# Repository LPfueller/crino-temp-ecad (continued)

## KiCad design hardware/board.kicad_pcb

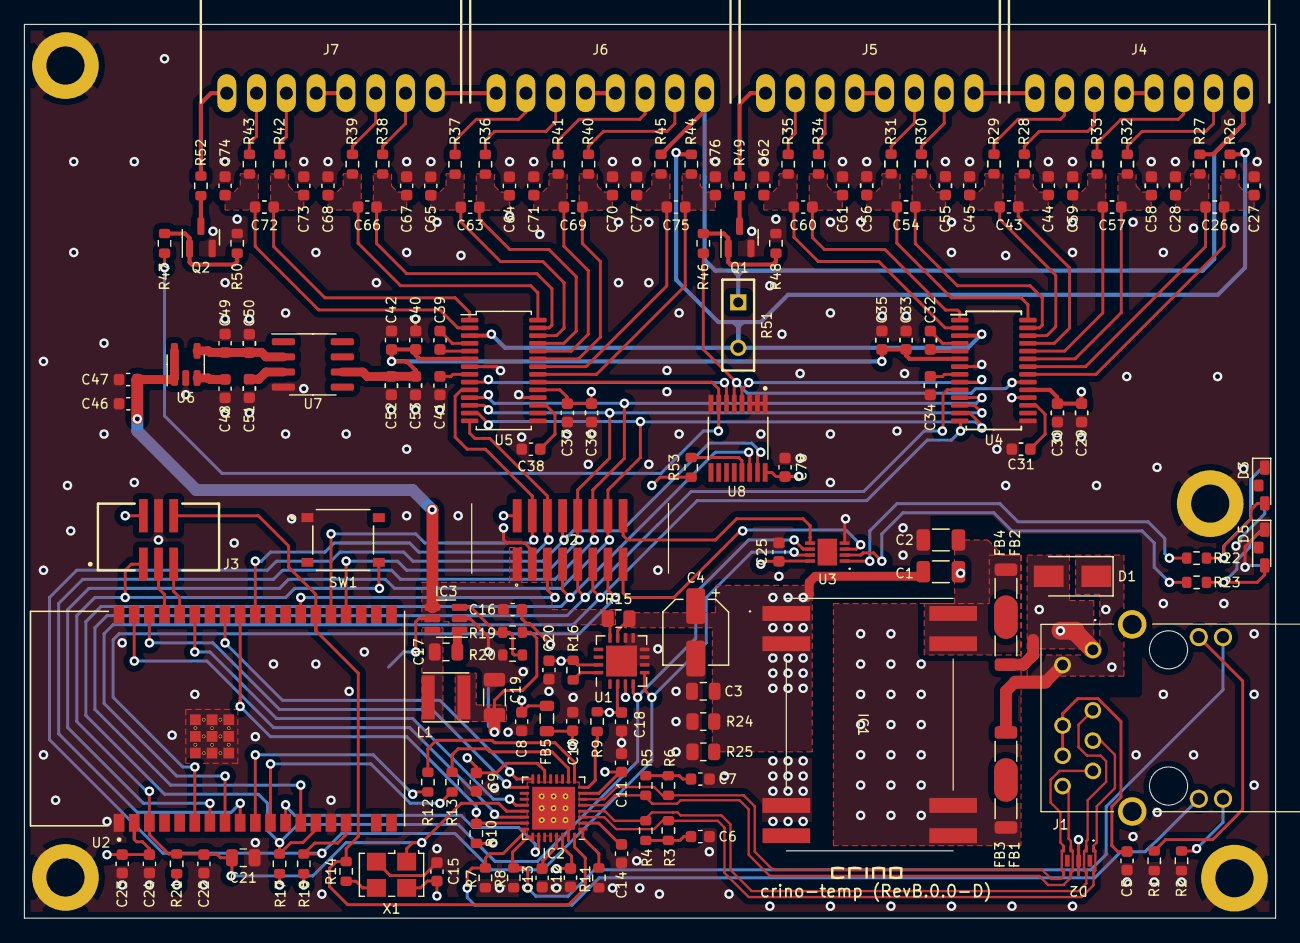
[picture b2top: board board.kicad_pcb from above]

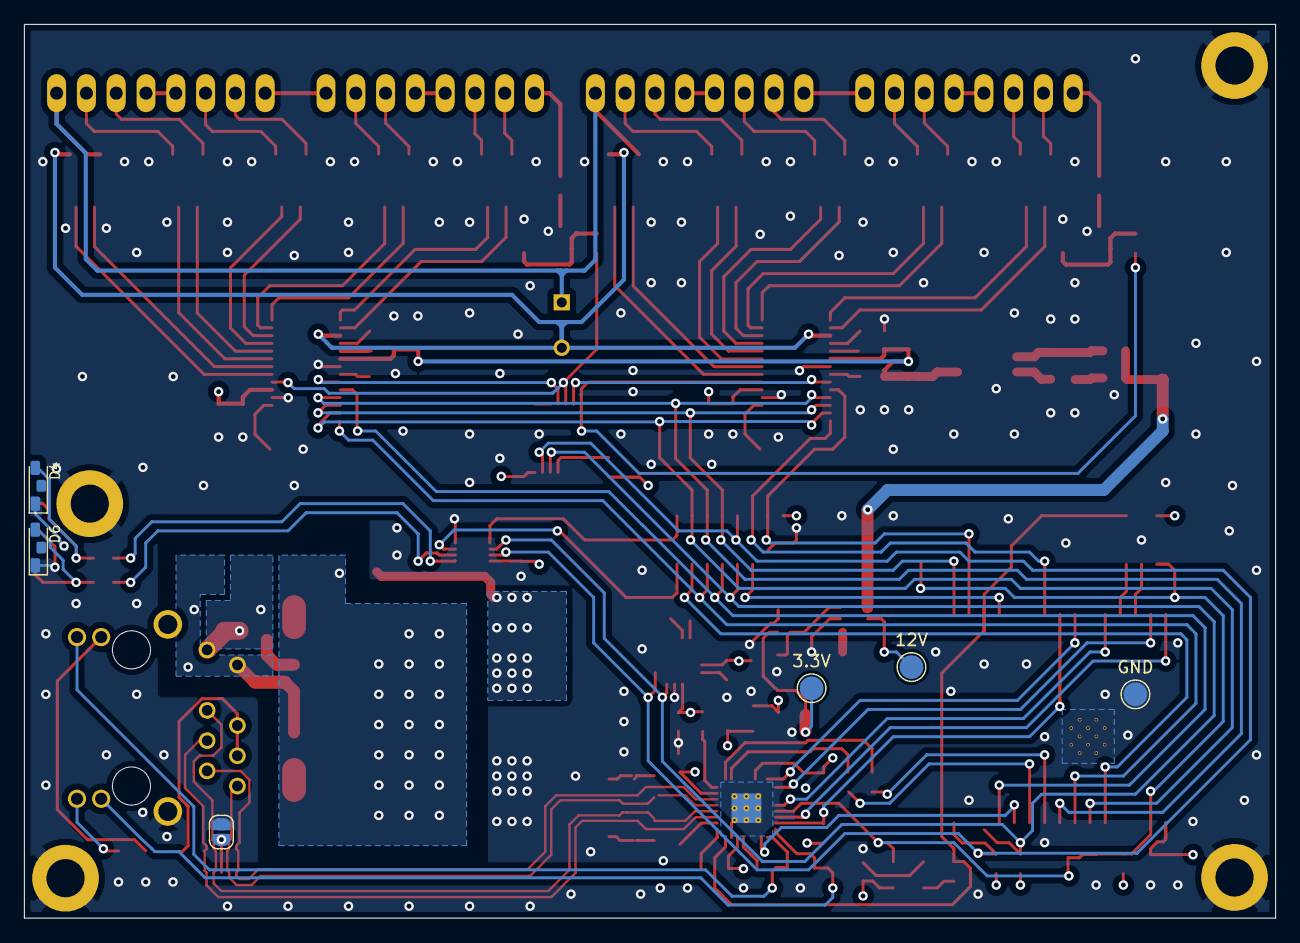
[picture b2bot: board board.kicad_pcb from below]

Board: 4 copper layers, 105.0 x 75.0 mm, 174 parts (6 on the bottom side), 130 nets.

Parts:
C1, C2: 4.7n; C_1206_3216Metric
C3: 10u; C_0805_2012Metric
C4: 100u; CP_Elec_5x5.4
C5: 22p; C_0603_1608Metric
C6, C7, C9, C11, C12, C13, C14, C15, C18, C20, C24, C25, C30, C33, C37, C40, C47, C48, C50, C53, C78: 100n; C_0603_1608Metric
C8, C10: 47u; C_0603_1608Metric
C16: 4.7u; C_0603_1608Metric
C17, C21: 100n; C_0805_2012Metric
C19: 22u; C_1206_3216Metric
C22, C29, C31, C34, C35, C36, C38, C41, C42, C51: 1u; C_0603_1608Metric
C23: 22u; C_0603_1608Metric
C26, C43, C54, C57, C60, C63, C66, C69, C72, C75: 22n; C_0603_1608Metric
C27, C28, C44, C45, C55, C56, C58, C59, C61, C62, C64, C65, C67, C68, C70, C71, C73, C74, C76, C77: 1n; C_0603_1608Metric
C32, C39: 4.7n; C_0603_1608Metric
C46, C49, C52: 2.2u; C_0603_1608Metric
D1: D_Schottky; D_SMA
D2: RCLAMP3374N.TCT; RCLAMP3374NTCT
D3, D4: LED_GREEN; LED_3210Metric_Right_Angle
D5, D6: LED_BLUE; LED_3210Metric_Right_Angle
FB1, FB2, FB3, FB4: FerriteBead; L_1206_3216Metric
FB5: FerriteBead; L_0805_2012Metric
H1, H2, H3, H4: MountingHole_Pad; MountingHole_3.2mm_M3_DIN965_Pad
H5: CrinoLogo; crino_logo
IC1: AG9912M
IC2: RTL8201F-VB-CG; QFN-32-1EP_5x5mm_P0.5mm_EP3.6x3.6mm_ThermalVias
IC3: SY8120B1ABC; SOT-23-6
J1: JXD1-0009NL; JXD10009NL
J2: SHF-108-01-L-D-SM; SHF-108-01-X-D-SM
J3: SHF-103-01-L-D-SM; SAMTEC_SHF-103-01-L-D-SM
J4, J5, J6, J7: WAGO-733-368; Wago_733-368
JP1: SolderJumper_2_Open; SolderJumper-2_P1.3mm_Open_RoundedPad1.0x1.5mm
L1: 4.7u; L_4.2x4.2_H2
Q1, Q2: 2N7002; SOT-23
R1, R2: 270; R_0603_1608Metric
R3, R4, R5, R6: 49.9; R_0603_1608Metric
R7, R8, R9, R10: 4.7k; R_0603_1608Metric
R11: 2.49k; R_0603_1608Metric
R12, R13, R14: 0; R_0603_1608Metric
R15: 0.68; R_0805_2012Metric
R16: 2.2k; R_0603_1608Metric
R17, R18: 5.6k; R_0603_1608Metric
R19, R48, R50: 100k; R_0603_1608Metric
R20: 22.1k; R_0603_1608Metric
R21, R53: 10k; R_0603_1608Metric
R22, R23: 100; R_0603_1608Metric
R24, R25: 750; R_0805_2012Metric
R26, R27, R28, R29, R30, R31, R32, R33, R34, R35, R36, R37, R38, R39, R40, R41, R42, R43, R44, R45: 10K; R_0603_1608Metric
R46, R47: 470; R_0603_1608Metric
R49, R52: 3.3k; R_0603_1608Metric
R51: 5K; Y14535K00000V9L
SW1: SW_Push; SW_TS-1187A-B-A-B
TP1: 12V; TestPoint_Pad_D2.0mm
TP2: 3.3V; TestPoint_Pad_D2.0mm
TP3: GND; TestPoint_Pad_D2.0mm
U1: PAC1932T-I/JQ; UQFN-16-1EP_4x4mm_P0.65mm_EP2.6x2.6mm
U2: ESP32-WROVER-E-N4R8
U3: PCA9536TK; SON50P300X300X100-9N-D
U4, U5: ADS1262IPW; TSSOP-28_4.4x9.7mm_P0.65mm
U6: LK112M80TR; SOT-23-5
U7: MAX6250; SOIC-8_3.9x4.9mm_P1.27mm
U8: PCA9534PWR; SOP65P640X120-16N
X1: SG-5032CCN; Oscillator_SMD_SeikoEpson_SG8002LB-4Pin_5.0x3.2mm

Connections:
/+3.3V: C8.1, C9.1, C15.1, C18.1, C19.1, C20.1, C23.1, C24.1, C25.1, C29.1, C30.1, C36.1, C37.1, C78.1, FB5.1, IC2.14 (DVDD33), J2.2, J3.2, L1.1, R9.1, R10.1, R16.2, R17.2, R18.2, R19.1, R21.1, R53.1, TP2.1, U1.2 (V_{DD}), U1.15 (V_{DD}IO), U2.2 (3V3), U3.8 (VDD), U4.19 (DVDD), U5.19 (DVDD), U8.16 (VCC), X1.4 (Vcc)
/+5VA: C33.1, C35.1, C40.1, C42.1, C52.2, C53.2, U4.6 (AVDD), U5.6 (AVDD), U7.6 (OUT)
/+12V: C16.1, C46.2, C47.2, IC3.4 (EN), IC3.5 (IN), J2.1, R15.1, TP1.1, U1.12 (SENSE1-), U6.1 (SHDN), U6.5 (IN)
/ADC1_!DRDY: J2.11, U2.8 (IO32), U4.14 (!DRDY)
/ADC1_CS: J2.9, U2.13 (IO14), U4.10 (!CS)
/ADC1_RST: R46.2, U4.20 (!RESET/PWDN), U8.5 (P1)
/ADC1_SRT: U4.9 (START), U8.4 (P0)
/ADC2_!DRDY: J2.6, U2.29 (IO5), U5.14 (!DRDY)
/ADC2_CS: J2.4, U2.24 (IO2), U5.10 (!CS)
/ADC2_RST: R47.2, U5.20 (!RESET/PWDN), U8.7 (P3)
/ADC2_SRT: U5.9 (START), U8.6 (P2)
/ADC_IDAC: R26.2, R44.2, R51.2, U4.3 (AINCOM), U5.3 (AINCOM)
/GND: C2.2, C3.2, C4.2, C5.2, C6.2, C7.2, C8.2, C9.2, C10.2, C11.2, C12.2, C13.2, C14.2, C15.2, C16.2, C18.2, C19.2, C20.2, C21.2, C22.2, C23.2, C24.2, C25.2, C27.2, C28.2, C29.2, C30.2, C31.2, C33.2, C34.1, C35.2, C36.2, C37.2, C38.2, C40.2, C41.1, C42.2, C44.2, C45.2, C46.1, C47.1, C48.1, C49.1, C50.1, C51.1, C52.1, C53.1, C55.2, C56.2, C58.2, C59.2, C61.2, C62.2, C64.2, C65.2, C67.2, C68.2, C70.2, C71.2, C73.2, C74.2, C76.2, C77.2, C78.2, D3.1 (K), D4.1 (K), D5.1 (K), D6.1 (K), H1.1, H2.1, H3.1, H4.1, IC1.3 (-VDC), IC2.31 (CKXTAL1), IC2.33 (EP), IC3.2 (GND), J1.MH2, J2.3, J3.4, JP1.2 (B), Q1.2 (S), Q2.2 (S), R1.1, R2.1, R7.2, R8.2, R11.1, R20.2, R24.2, R25.2, R48.1, R50.1, SW1.1, TP3.1, U1.3 (GND), U1.6 (ADDRSEL), U1.7 (GND), U1.8 (GND), U1.9 (GND), U1.10 (GND), U1.17 (EP), U2.1 (GND), U2.15 (GND), U2.38 (GND), U2.39_1 (EXP), U2.39_2 (EXP), U2.39_3 (EXP), U2.39_4 (EXP), U2.39_5 (EXP), U2.39_6 (EXP), U2.39_7 (EXP), U2.39_8 (EXP), U2.39_9 (EXP), U3.4 (VSS), U4.7 (AVSS), U4.15 (XTAL1/CLKIN), U4.18 (DGND), U5.7 (AVSS), U5.15 (XTAL1/CLKIN), U5.18 (DGND), U6.2 (GND), U7.4 (GND), U8.1 (A0), U8.2 (A1), U8.3 (A2), U8.8 (GND), X1.2 (GND)
/I2C_SCL: J2.7, R17.1, U1.4 (SCL), U2.14 (IO12), U3.6 (SCL), U8.14 (SCL)
/I2C_SDA: J2.8, R18.1, U1.5 (SDA), U2.16 (IO13), U3.7 (SDA), U8.15 (SDA)
/REF1_FILTERED_N: C26.2, C28.1, R27.1, U4.22 (AIN1)
/REF1_FILTERED_P: C26.1, C27.1, R26.1, U4.21 (AIN0)
/REF2_FILTERED_N: C75.2, C77.1, R45.1, U5.22 (AIN1)
/REF2_FILTERED_P: C75.1, C76.1, R44.1, U5.21 (AIN0)
/REF_N: J4.1, J6.1, R27.2, R45.2, R51.1
/SPI_CLK: J2.12, U2.9 (IO33), U4.11 (SCLK), U5.11 (SCLK)
/SPI_MISO: J2.14, U2.7 (IO35), U4.13 (DOUT), U5.13 (DOUT)
/SPI_MOSI: J2.10, U2.23 (IO15), U4.12 (DIN), U5.12 (DIN)
/TEMP1_FILTERED_N: C57.2, C59.1, R33.1, U4.24 (AIN3)
/TEMP1_FILTERED_P: C57.1, C58.1, R32.1, U4.23 (AIN2)
/TEMP1_N: J4.3, R33.2
/TEMP1_P: J4.2, R32.2
/TEMP2_FILTERED_N: C43.2, C45.1, R29.1, U4.26 (AIN5)
/TEMP2_FILTERED_P: C43.1, C44.1, R28.1, U4.25 (AIN4)
/TEMP2_N: J4.7, R29.2
/TEMP2_P: J4.6, R28.2
/TEMP3_FILTERED_N: C54.2, C56.1, R31.1, U4.28 (AIN7)
/TEMP3_FILTERED_P: C54.1, C55.1, R30.1, U4.27 (AIN6)
/TEMP3_N: J5.3, R31.2
/TEMP3_P: J5.2, R30.2
/TEMP4_FILTERED_N: C60.2, C62.1, R35.1, U4.2 (AIN9)
/TEMP4_FILTERED_P: C60.1, C61.1, R34.1, U4.1 (AIN8)
/TEMP4_N: J5.7, R35.2
/TEMP4_P: J5.6, R34.2
/TEMP5_FILTERED_N: C69.2, C71.1, R41.1, U5.24 (AIN3)
/TEMP5_FILTERED_P: C69.1, C70.1, R40.1, U5.23 (AIN2)
/TEMP5_N: J6.3, R41.2
/TEMP5_P: J6.2, R40.2
/TEMP6_FILTERED_N: C63.2, C65.1, R37.1, U5.26 (AIN5)
/TEMP6_FILTERED_P: C63.1, C64.1, R36.1, U5.25 (AIN4)
/TEMP6_N: J6.7, R37.2
/TEMP6_P: J6.6, R36.2
/TEMP7_FILTERED_N: C66.2, C68.1, R39.1, U5.28 (AIN7)
/TEMP7_FILTERED_P: C66.1, C67.1, R38.1, U5.27 (AIN6)
/TEMP7_N: J7.3, R39.2
/TEMP7_P: J7.2, R38.2
/TEMP8_FILTERED_N: C72.2, C74.1, R43.1, U5.2 (AIN9)
/TEMP8_FILTERED_P: C72.1, C73.1, R42.1, U5.1 (AIN8)
/TEMP8_N: J7.7, R43.2
/TEMP8_P: J7.6, R42.2
/mcu/ESP_EN: C21.1, C22.1, IC2.21 (PHYRSTB), J3.1, R21.2, SW1.2, U2.3 (EN), X1.1 (OE)
/mcu/GPI34: J2.13, U2.6 (IO34)
/mcu/GPIO0: IC2.32 (CKXTAL2), J3.6, R14.2, U2.25 (IO0)
/mcu/GPIO4: J2.5, U2.26 (IO4)
/mcu/I2C_GPIO1: J2.15, U3.3 (IO2)
/mcu/I2C_GPIO2: J2.16, U3.5 (IO3)
/mcu/esp32/GPIO18_MDIO(RMII): IC2.23 (MDI_O), R10.2, U2.30 (IO18)
/mcu/esp32/GPIO19_EMAC_TXD0(RMII): IC2.16 (TXD[0]), U2.31 (IO19)
/mcu/esp32/GPIO21_EMAC_TX_EN(RMII): IC2.20 (TXEN), U2.33 (IO21)
/mcu/esp32/GPIO22_EMAC_TXD1(RMII): IC2.17 (TXD[1]), U2.36 (IO22)
/mcu/esp32/GPIO23_MDC(RMII): IC2.22 (MDC), U2.37 (IO23)
/mcu/esp32/GPIO25_EMAC_RXD0(RMII): R12.2, U2.10 (IO25)
/mcu/esp32/GPIO26_EMAC_RXD1(RMII): R13.2, U2.11 (IO26)
/mcu/esp32/GPIO27_EMAC_RX_CRS_DV: IC2.26 (CRS/CRS_DV), U2.12 (IO27)
/mcu/esp32/RXD0: J3.5, U2.34 (RXD0)
/mcu/esp32/TXD0: J3.3, U2.35 (TXD0)
/mcu/ethernet/AVDD: C10.1, C11.1, C12.1, FB5.2, IC2.7 (AVDD33_1), IC2.30 (AVDD33_2)
/mcu/ethernet/RD+: D2.4 (LINE_3_IN), D2.7 (LINE_3_OUT), IC2.5 (MDI+[1]), J1.10 (RD+), R5.1
/mcu/ethernet/RD-: D2.5 (LINE_4_IN), D2.6 (LINE_4_OUT), IC2.6 (MDI_-[1]), J1.9 (RD-), R6.1
/mcu/ethernet/TD+: D2.1 (LINE_1_IN), D2.10 (LINE_1_OUT), IC2.3 (MDI+[0]), J1.7 (TD+), R3.1
/mcu/ethernet/TD-: D2.2 (LINE_2_IN), D2.9 (LINE_2_OUT), IC2.4 (MDI_-[0]), J1.5 (TD-), R4.1
/mcu/ethernet/V+: D1.1 (K), FB1.1, J1.2 (V+)
/mcu/ethernet/V-: D1.2 (A), FB2.1, J1.1 (V-)
/mcu/io/LED1: R22.1, U3.1 (IO0)
/mcu/io/LED2: R23.1, U3.2 (IO1)
/mcu/poe/+12V_INTERNAL: C1.2, C3.1, C4.1, IC1.1 (+VDC_1), IC1.2 (+VDC_2), R15.2, R24.1, R25.1, U1.11 (SENSE1+)
unnamed: C1.1, FB3.2, IC1.5 (VIN+_1), IC1.6 (VIN+_2)
unnamed: C2.1, FB4.2, IC1.7 (VIN-_1), IC1.8 (VIN-_2)
unnamed: C5.1, J1.6 (TCT), J1.8 (RCT)
unnamed: C6.1, R3.2, R4.2
unnamed: C7.1, R5.2, R6.2
unnamed: C13.1, IC2.29 (DVDD10OUT)
unnamed: C14.1, IC2.2 (AVDD10OUT)
unnamed: C17.1, IC3.1 (BS)
unnamed: C17.2, IC3.6 (LX), L1.2
unnamed: C31.1, U4.17 (BYPASS)
unnamed: C32.1, U4.5 (CAPN)
unnamed: C32.2, U4.4 (CAPP)
unnamed: C34.2, U4.8 (REFOUT)
unnamed: C38.1, U5.17 (BYPASS)
unnamed: C39.1, U5.5 (CAPN)
unnamed: C39.2, U5.4 (CAPP)
unnamed: C41.2, U5.8 (REFOUT)
unnamed: C48.2, U6.3 (Bypass)
unnamed: C49.2, C50.2, U6.4 (OUT), U7.2 (IN)
unnamed: C51.2, U7.3 (NR)
unnamed: D2.3 (GND), D2.8 (GND), D2.12 (GND), JP1.1 (A)
unnamed: D3.2 (A), D4.2 (A), R22.2
unnamed: D5.2 (A), D6.2 (A), R23.2
unnamed: FB1.2, FB3.1
unnamed: FB2.2, FB4.1
unnamed: IC2.1 (RSET), R11.2
unnamed: IC2.8 (RXDV), R9.2
unnamed: IC2.9 (RXD[0]), R12.1
unnamed: IC2.10 (RXD[1]), R13.1
unnamed: IC2.24 (LED0/_PHYAD[0]/PMEB), J1.11 (ANODE_YELLOW), R7.1
unnamed: IC2.25 (LED1/PHYAD[1]), J1.14 (ANODE_GREEN), R8.1
unnamed: IC3.3 (FB), R19.2, R20.1
unnamed: J1.12 (KATHODE_YELLOW), R2.2
unnamed: J1.13 (KATHODE_GREEN), R1.2
unnamed: J4.4, J4.5
unnamed: J4.8, J5.1
unnamed: J5.4, J5.5
unnamed: J5.8, R49.1
unnamed: J6.4, J6.5
unnamed: J6.8, J7.1
unnamed: J7.4, J7.5
unnamed: J7.8, R52.1
unnamed: Q1.1 (G), R46.1, R48.2
unnamed: Q1.3 (D), R49.2
unnamed: Q2.1 (G), R47.1, R50.2
unnamed: Q2.3 (D), R52.2
unnamed: R14.1, X1.3 (OUT)
unnamed: R16.1, U1.16 (~PWRDN)
unnamed: R53.2, U8.13 (~INT)

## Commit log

2024-02-29 Backlink to CADLAB.io has been added.
